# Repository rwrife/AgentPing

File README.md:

# AgentPing

**A tiny desk-side inbox for AI coding agents.**

AgentPing puts an animated 3D robot on either a **Waveshare ESP32-C6 Touch AMOLED 1.64** (280 × 456 portrait) or **Waveshare ESP32-S3-LCD-1.47B** (172 × 320 portrait). A Windows USB worker connects it to **Codex, Claude Code, and GitHub Copilot CLI**. Agent notifications show a provider logo and message; CLI and MCP controls let you play animations, pose limbs, and display custom icons.

The physical robot uses `live3d_usb` on C6 or `live3d_usb_s3` on S3. Both share the same robot, USB protocol, Windows client, and agent integrations. This path needs **USB only**: no Wi-Fi, .NET bridge, tray app, Node.js, or simulator is required.

| Board | Display / input | Firmware environment | Purchase |
| --- | --- | --- | --- |
| ESP32-C6-Touch-AMOLED-1.64 | 280 × 456 AMOLED, touch | `live3d_usb` | [Amazon](https://www.amazon.com/dp/B0GTDXXYV8) |
| ESP32-S3-LCD-1.47B | 172 × 320 LCD, **no touch** | `live3d_usb_s3` | [Amazon](https://www.amazon.com/dp/B0FBWPJPXN) / [Waveshare specifications](https://www.waveshare.com/ESP32-S3-LCD-1.47B.htm) |

The S3 passed [on-device smoke tests](firmware/BRINGUP-S3.md) for USB commands,
rendering and desktop controls. Physical LCD appearance and enclosure fit still
need verification. Select the exact **1.47B**, not the non-B S3 board.
The optional network/touch application remains C6-only. Board-specific
[3D-print enclosure files and fit notes](hardware/enclosure/README.md) are separate;
do not print the C6 enclosure for the S3.
Both enclosures share the C6 rounded snap-fit design and identical rear vents,
so the same [monitor arm and desktop stand](hardware/enclosure/mounts/README.md)
fit either version.

## Quick start: physical robot on Windows

### 1. Buy the board and prepare Windows

1. Choose either display board from the table above. Check the exact listing
   variant; a bare ESP32 development board or a different display revision
   will not work with these pin assignments and enclosure dimensions.
2. Have a USB **data** cable ready. The same connection powers the board and carries
   commands; a charge-only cable will not expose a serial port.
3. Install Git and Python 3.11 or newer (tested with 3.13), with their commands
   available on PATH. Open a new PowerShell terminal and check:

```powershell
git --version
python --version
```

Install and sign into your chosen agent CLIs separately. The USB Windows client
below is a background Python application controlled by `robot.cmd`; the optional
.NET tray application has separate instructions later in this guide.

### 2. Download the project and install the Windows USB client

```powershell
git clone https://github.com/rwrife/AgentPing.git
cd AgentPing
.\companion\setup-robot.ps1
```

Setup creates `.venv-robot` and installs the USB and MCP dependencies. Wait for
the `Ready` message, then check the launcher:

```powershell
.\companion\robot.cmd --help
```

If PowerShell blocks the setup script, perform the same installation directly:

```powershell
python -m venv .venv-robot
.\.venv-robot\Scripts\python.exe -m pip install -r tools/requirements-robot.txt
```

For an existing checkout, preserve local work, then use `git switch main` and
`git pull --ff-only`. Run setup again when Python dependencies change. All commands
below run from the repository root; virtual environment activation is unnecessary.

### 3. Build the firmware

Skip steps 3–4 if the board already has the current USB robot firmware for its model.
Create a separate build environment, install the pinned dependencies, and compile:

```powershell
python -m venv .venv-firmware
.\.venv-firmware\Scripts\python.exe -m pip install -r firmware/requirements-ci.txt
$firmwareEnv = "live3d_usb" # C6; use "live3d_usb_s3" for ESP32-S3-LCD-1.47B
.\.venv-firmware\Scripts\pio.exe run -d firmware -e $firmwareEnv
```

Wait for `[SUCCESS]`. The first build downloads the ESP-IDF toolchain and can take
several minutes. The output is `firmware/.pio/build/<environment>/firmware.bin`.
Use **`-e $firmwareEnv`** explicitly; the default C6 network firmware is a different
application. Model, textures, and animations are checked in, so FBX conversion,
Node.js, and the simulator are not needed. See [live renderer details](firmware/LIVE3D.md).

### 4. Connect and flash the board

1. Plug the board into the PC using the USB data cable.
2. Find its serial port in Device Manager under **Ports (COM & LPT)**, or run:

```powershell
.\.venv-robot\Scripts\python.exe -m serial.tools.list_ports
```

3. Replace `COM5` below with the reported port. Close serial monitors and stop an
   existing robot worker before flashing:

```powershell
# Only needed if a worker is already running:
.\companion\robot.cmd stop

.\.venv-firmware\Scripts\pio.exe run -d firmware -e $firmwareEnv -t upload --upload-port COM5
```

4. Wait for the upload's `[SUCCESS]` message and automatic reset. The robot should
   play its startup sequence and enter idle with the initial connection message.
   If no port appears, try another data cable/USB port before retrying.
   On S3, if automatic download fails, hold **BOOT**, tap **RESET**, release
   **BOOT**, and check the COM port again before uploading. Tap **RESET** after
   flashing if it remains in download mode. Keep both buttons clear of the enclosure.

### 5. Start the Windows USB client and verify the display

```powershell
.\companion\robot.cmd start
.\companion\robot.cmd status
```

A successful live response includes `"ok": true` and `VIEW state=...`. Wait a few seconds after plugging in or resetting the device before checking status. One background worker owns USB for both notifications and MCP.

```powershell
.\companion\robot.cmd worker-status  # Worker health and delivery counters
.\companion\robot.cmd reset          # Return to idle
.\companion\robot.cmd stop           # Release USB before flashing
```

Start the worker again after restarting Windows; setup does not install an automatic startup service. The initial connection caption disappears after the first desktop signal.

Send the first message:

```powershell
.\companion\robot.cmd message "Hello world!"
```

Look for `PAL STATE attention OK` in the command response and a waving robot with
a message bubble on the device. The client runs in the background, so no app window
is expected. Continue with the [terminal demo](#terminal-demo), then
[wire up your CLI agents](#wire-up-the-cli-agents) for automatic notices and MCP.

## Terminal demo

From the repository root, start the worker with `.\companion\robot.cmd start`.
Run the examples **one at a time**, leaving time to see each state. Sending the
next command replaces the current animation or message.

### Startup, thinking, and attention

```powershell
.\companion\robot.cmd state boot
.\companion\robot.cmd message "Consulting my rubber duck..." --state thinking
.\companion\robot.cmd message "Your approval is needed!"
.\companion\robot.cmd message "The changes are ready. Please review the pull request." --state attention
.\companion\robot.cmd reset
```

### Error messages

These demonstrate the error animation, close-up, and message bubble without
causing an actual failure:

```powershell
.\companion\robot.cmd message "Build failed: please check the terminal." --state error
.\companion\robot.cmd message "Tests failed. I need your help!" --state error
.\companion\robot.cmd message "Connection lost. Please check the USB cable." --state error
.\companion\robot.cmd reset
```

### Custom icons and Teams demo

```powershell
.\companion\robot.cmd icon --file assets/icons/heart-48.bin --color "#ff8800" --message "Hello world!"
.\companion\robot.cmd icon --file assets/icons/teams-48.bin --color "#8b88ff" --message "Teams: Your meeting starts now"
.\companion\robot.cmd icon --file assets/icons/enghub.bin --color "#0078D4" --message "EngHub: Your review is needed"

# Error state overrides the requested green/purple and renders the icon red.
.\companion\robot.cmd icon --file assets/icons/heart-48.bin --color "#00ff00" --state error --message "Demo error: something needs fixing!"
.\companion\robot.cmd icon --file assets/icons/teams-48.bin --color "#8b88ff" --state error --message "Teams demo: unable to join the meeting."
.\companion\robot.cmd reset
```

The Teams icon is a demo graphic; these commands do not connect to Teams.

### Dances and limb controls

```powershell
.\companion\robot.cmd dance chicken
.\companion\robot.cmd dance twist
.\companion\robot.cmd dance twist
.\companion\robot.cmd reset
.\companion\robot.cmd joint right_shoulder --z -90 --duration-ms 1000
.\companion\robot.cmd joint head --y 25 --duration-ms 800
.\companion\robot.cmd reset
```

### Short automatic demo

Paste this whole block to cycle through thinking, attention, and a red Teams-style
error icon, with six seconds to view each notice, then finish in idle:

```powershell
.\companion\robot.cmd start
.\companion\robot.cmd message "Thinking through the next step..." --state thinking
Start-Sleep -Seconds 6
.\companion\robot.cmd message "Ready for your review!" --state attention
Start-Sleep -Seconds 6
.\companion\robot.cmd icon --file assets/icons/teams-48.bin --color "#8b88ff" --state error --message "Demo error: please check the terminal."
Start-Sleep -Seconds 6
.\companion\robot.cmd reset
```

Messages and custom icons dismiss after 30 seconds and return to idle. Error icons are always red, overriding the requested color. Manual joint poses hold until reset or another state; offsets are relative to the captured animation pose. These move the rendered skeleton. Full command and bitmap details: [robot controls](docs/robot-control.md).

## Wire up the CLI agents

| Connection | Purpose | Setup |
| --- | --- | --- |
| Notification hooks | Automatically show permission/input requests, completion, and supported errors | Install hooks below |
| MCP tools | Let an agent deliberately show messages, dance, move joints, or send icons | Register MCP in each client |

Both share the USB worker. MCP registration alone does not install notification hooks. Hooks notify you; they do not approve, deny, or resume agent tasks.

Automatic thinking notices are limited to once every two minutes across all
agents. Repeats are dropped so the message can dismiss after 30 seconds and return
to idle. Attention and error notices still get through immediately. Explicit
CLI/MCP demo commands bypass this cooldown.

### Automatic notifications

Preview the configuration paths, then install the additive hooks for all three providers:

```powershell
.\.venv-robot\Scripts\python.exe tools/install_usb_hooks.py
.\.venv-robot\Scripts\python.exe tools/install_usb_hooks.py --apply
.\companion\robot.cmd start
```

The installer preserves unrelated handlers and backs up existing settings under `%USERPROFILE%\.agentping\usb\backups`.

| Agent | Configuration written | Events wired |
| --- | --- | --- |
| Codex | `%USERPROFILE%\.codex\hooks.json` | `UserPromptSubmit`, `PostToolUse`, `PermissionRequest`, `Stop` |
| Claude Code | `%USERPROFILE%\.claude\settings.json` | `PermissionRequest`, `Notification`, `Stop`, `StopFailure` |
| Copilot CLI | `%USERPROFILE%\.copilot\hooks\agentping-usb.json` | `userPromptSubmitted`, `permissionRequest`, `postToolUse`, `notification`, `awaitingUserInput`, `agentStop`, `errorOccurred` |

Restart your CLI sessions after installation. **In Codex, open `/hooks` and review/trust the AgentPing entries**; untrusted hooks are skipped. Rerun the installer after moving the checkout, replacing its Python environment, or updating the hook implementation.

Run a normal task in each agent, then check `robot.cmd worker-status` for an incremented provider delivery counter and inspect the display. Claude and Copilot live completion hooks were verified during bring-up. Codex's injected permission event was verified, but live Codex hook delivery still requires review/activation and validation in your session. See [notification details and tested versions](docs/usb-notifications.md).

For a **synthetic pipeline test**, not proof of a live agent event:

```powershell
'{}' | .\.venv-robot\Scripts\python.exe tools/agentping_usb_notifications.py hook --provider codex --event PermissionRequest
Start-Sleep -Seconds 2
.\companion\robot.cmd worker-status
```

### MCP registration in each CLI

**Copilot CLI on Windows:** this repository includes [`.github/mcp.json`](.github/mcp.json).
After installing the desktop tools, launch Copilot from the repository root:

```powershell
.\companion\robot.cmd start
copilot mcp list
copilot
```

Accept the repository trust prompt, then use `/mcp show agentping` to inspect the
connection. The configuration uses the relative `companion\robot.cmd` launcher,
so start Copilot in the repository root. No user-level registration is needed
for this checkout. The USB worker must already be running. Use the registration
commands below if you want the robot available from other repositories too.

With the worker running, resolve the checkout paths in PowerShell:

```powershell
$robotPython = (Resolve-Path .\.venv-robot\Scripts\python.exe).Path
$robotServer = (Resolve-Path .\tools\agentping_robot.py).Path
```

Run the registration command for each installed client you want to use:

```powershell
# Codex
codex mcp add agentping -- "$robotPython" "$robotServer" mcp
codex mcp list

# Claude Code: available across your projects
claude mcp add --transport stdio --scope user agentping -- "$robotPython" "$robotServer" mcp
claude mcp list

# GitHub Copilot CLI
copilot mcp add agentping -- "$robotPython" "$robotServer" mcp
copilot mcp list
```

Reconnect/restart the agent session and inspect its MCP tools. If an `agentping` entry exists, inspect/update it instead of registering a duplicate. For older Copilot CLI versions without `copilot mcp add`, use interactive `/mcp add`: local/stdio, the Python executable above, and the script path plus `mcp` as arguments.

Official references: [Codex MCP](https://developers.openai.com/codex/mcp), [Claude Code MCP](https://code.claude.com/docs/en/mcp), and [Copilot CLI MCP](https://docs.github.com/en/copilot/how-tos/copilot-cli/customize-copilot/add-mcp-servers). Command syntax was also checked against the installed CLIs.

For another MCP client, configure a **stdio** server with the Python executable as its command and `[absolute-script-path, "mcp"]` as its two arguments. A complete JSON example is in [robot-control.md](docs/robot-control.md#mcp-configuration). The client launches MCP; start the USB worker separately.

Available tools: `robot_status`, `robot_message`, `robot_animation`, `robot_dance`, `robot_move_joint`, `robot_icon`, and `robot_reset`.

Example demo prompts:

> Use AgentPing to show "Hello world!", then do the chicken dance.

> Reset the robot, turn its head 25 degrees on Y over 800 milliseconds, then reset it again.

> Show "Waiting for your approval" on the robot in the attention state.

> Use AgentPing's robot_message tool with state "error" to show "Build failed: please check the terminal." Leave it visible.

> Read assets/icons/teams-48.bin as hexadecimal and use AgentPing's robot_icon tool with color "#8b88ff", state "error", and message "Teams demo: unable to join the meeting." The device should show the icon in red.

> Use AgentPing's robot_reset tool to clear the demo and return to idle.

### Verify and troubleshoot

```powershell
# Software checks; no board required
.\.venv-robot\Scripts\python.exe -m unittest discover -s tools/tests

# MCP-to-device smoke test; changes poses/messages and ends in idle
.\.venv-robot\Scripts\python.exe tools/check_robot_mcp.py
```

- **USB unavailable/no acknowledgment:** check the data cable and USB port, close serial monitors, then run `robot.cmd stop`. Reconnect or reset the board, wait for boot, and run `robot.cmd start` followed by `robot.cmd status`. The worker finds the board by USB VID/PID, so it does not matter which port it is plugged into.
- **MCP tools missing:** check the registered absolute paths, reconnect the client, and confirm `.venv-robot` exists. MCP speaks a machine protocol over stdio; it does not present a terminal UI.
- **MCP works but automatic notices do not:** check hook installation and provider-session reload; review Codex `/hooks`. Compare delivery counters before/after a real event. Identical provider events can be coalesced for three seconds.
- **Firmware upload fails:** stop the worker and other serial clients, then flash the correct board environment (`live3d_usb` or `live3d_usb_s3`) on the correct port.

USB rendering, CLI/MCP control, provider logos, red error icons, and timed return to idle have been tested on the physical C6 device; the S3 needs the same bench checks. Notifications replace the visible notice; there is no on-device queue or approval-response flow.

## Forward Windows notifications

The Windows companion can send new notifications from selected apps to the USB
robot, including the app's logo and message. Open **Windows notifications** in the
packaged companion to grant access and select apps. Messages show for 30 seconds,
then the robot returns to idle.

See [Windows notification setup](docs/windows-notifications.md) for the Windows 11
package build/install commands, permission setup, and testing steps. The USB host
must be running; the network bridge is not required.

## Optional network bridge and tray application

### Build and launch the Windows tray app

This is the separate .NET management UI for the network bridge. It does not start
or replace the USB robot worker above. For the USB demo, use `robot.cmd`.

1. Install a **stable .NET 10.0 SDK**. `global.json` selects the latest installed
   10.0 feature band or patch (10.0.100 or newer).
   Confirm it appears in `dotnet --list-sdks`.
2. From the repository root, restore the solution and publish the app and its
   companion bridge together:

```powershell
dotnet restore AgentPing.sln --locked-mode
dotnet publish companion/AgentPing.Companion.Windows/AgentPing.Companion.Windows.csproj -c Release -r win-x64 --self-contained true --no-restore -o artifacts/win-x64/app
dotnet publish bridge/AgentPing.Bridge/AgentPing.Bridge.csproj -c Release -r win-x64 --self-contained true --no-restore -o artifacts/win-x64/app/bridge
```

3. Launch the published application:

```powershell
Start-Process -FilePath .\artifacts\win-x64\app\AgentPing.Companion.exe -WindowStyle Normal
```

4. Use its management window/tray icon for bridge controls. For ARM64 Windows,
   replace `win-x64` with `win-arm64` in all publish and launch paths.
   Keep the complete output folder, including `bridge/`, together when moving it.

Publishing self-contained includes the .NET runtime. These local builds are
unsigned. Network device pairing requires additional TLS/provisioning setup;
see [companion details](companion/README.md) and
[Windows troubleshooting](docs/windows-troubleshooting.md).

### Bridge

- ASP.NET Core 10 executable with structured JSON console logging
- loopback-only default listener at `http://127.0.0.1:8742`
- `GET /health` and non-secret protocol-v1 `GET /api/status`
- strict, 16 KiB-bounded `POST /api/events` and `POST /api/attentions` ingestion
- deterministic session/attention state, contiguous ingress ordering, idempotency, bounded history, transactional atomic persistence, stale-session handling, and restart recovery
- digest-authenticated protocol-v1 `/ws` capability negotiation, heartbeat validation, reconnect replay, and live state fan-out
- integration tests, process-level smoke coverage, and a reproducible Docker image build
- default-off, loopback-only adapters for Codex CLI, Claude Code, and Copilot CLI hooks, with bounded secret-redacted mapping, durable approve/deny outcomes, and synthetic fixtures

### Windows companion

- Windows Forms tray controls and live bridge/device/adapter/attention status
- explicit private-interface TLS pairing, bounded discovery, token rotation/revocation, and redacted log export
- current-user DPAPI credential protection, opt-in startup, high-DPI/accessibility metadata, and `.resx` localization extension points
- signed-ready WiX packaging plus explicitly unsigned `win-x64` and `win-arm64` CI artifacts

### Firmware

- pinned PlatformIO 6.1.18 / ESP-IDF 5.5.0 ESP32-C6 project with locked managed components
- compile-tested CO5300 AMOLED, FT6146 touch, and LVGL initialization from pinned Waveshare schematic/BSP evidence
- accessible disconnected/idle/running/waiting/completed/error UI with burn-in movement plus touch approve/deny/cancel/acknowledge/reply controls and two-tap destructive confirmation
- strict host-tested protocol parser/action policy/state reducer, authenticated WSS capability/heartbeat/replay/action transport, persistent resume state, and bounded reconnect backoff
- USB-serial NVS provisioning and physical factory reset with no hardcoded network/provider credentials or secret-bearing logs

### Protocol contract

- JSON Schema Draft 2020-12 contract for all nine v1 message kinds
- bounded envelopes, revisioned/idempotent actions, version negotiation, and reconnect/resume rules
- LAN threat model and full-entropy token pairing/rotation/revocation design
- golden valid/fail-closed fixtures consumed by Python validation and bridge serialization tests

The network firmware described in this section has compile/host-test evidence; USB robot validation does not validate its Wi-Fi, touch actions, or network pairing. The bridge implements protected credential lifecycle and TLS-only enrollment; operators must separately configure the RFC1918 Kestrel HTTPS/WSS endpoint and certificate. Provider permission decisions were not exercised with live provider accounts.

## Repository layout

```text
bridge/       ASP.NET Core bridge and tests
firmware/     shared robot, C6/S3 board drivers, native tests, and bring-up guides
protocol/     shared machine-readable protocol schema, fixtures, and validator
hardware/     hardware scope and future editable KiCad sources
docs/         architecture and protocol status
integration/  process-level integration tooling
scripts/      canonical local verification command
```

## Optional Pixel Pal portrait simulator

Preview the imported Meshy FBX and dynamic face states locally at the device's
280 × 456 portrait resolution. Run `npm ci` then `npm run dev` from `simulator/`
and open `http://127.0.0.1:5173`. See [simulator/README.md](simulator/README.md)
for controls, validation, asset provenance, and the strategy for moving to hardware.

## Build and test the bridge

Requires the .NET 10 SDK.

```bash
dotnet restore AgentPing.sln --locked-mode
dotnet build AgentPing.sln --configuration Release --no-restore
dotnet test AgentPing.sln --configuration Release --no-build
./integration/smoke-bridge.sh
```

Run the service:

```bash
dotnet run --project bridge/AgentPing.Bridge
curl http://127.0.0.1:8742/health
curl http://127.0.0.1:8742/api/status
```

Expected health response: `Healthy`. The status JSON identifies `agentping-bridge`, reports `status: ok`, uses protocol `apiVersion: 1.0`, and exposes only non-secret session/attention/history counts plus the latest server sequence. See [`bridge/README.md`](bridge/README.md) for ingestion, authenticated WebSocket, persistence, and configuration details.

## Build the firmware

```bash
python3 -m venv .venv-platformio
. .venv-platformio/bin/activate
python3 -m pip install --requirement firmware/requirements-ci.txt
python3 -m pip install --requirement protocol/requirements-ci.txt
firmware/tests/run_host_tests.sh
python3 protocol/validate.py
platformio run -d firmware
```

These commands build the C6 network firmware. CI compilation does not validate physical Wi-Fi, touch, or pairing behavior. Use the explicit board-specific USB instructions above for the robot. See [`firmware/README.md`](firmware/README.md).

## Container build

```bash
docker build --file bridge/AgentPing.Bridge/Dockerfile --tag agentping-bridge:local .
docker run --rm -p 127.0.0.1:8742:8742 agentping-bridge:local
```

The container listens on `0.0.0.0:8742` inside its isolated network namespace so Docker can forward traffic; the documented host publish is explicitly restricted to `127.0.0.1`.

## Architecture and protocol

The ESP32 remains a thin client; provider credentials stay on the PC. The bridge binds to loopback by default. LAN pairing requires a separately configured RFC1918 HTTPS/WSS endpoint and certificate; the default HTTP listener must never be exposed to the LAN.

- [`docs/architecture.md`](docs/architecture.md) describes current and planned boundaries.
- [`docs/protocol.md`](docs/protocol.md) specifies protocol v1, secure pairing, compatibility, ordering, resume, and fail-closed action rules.
- [`docs/generated/protocol-v1-reference.md`](docs/generated/protocol-v1-reference.md) is generated directly from the canonical schema.
- [`docs/provider-adapters.md`](docs/provider-adapters.md) documents default-off Codex CLI, Claude Code, Copilot CLI, and manual/test hook ingestion.
- [`docs/release/mvp-release-runbook.md`](docs/release/mvp-release-runbook.md), [`docs/release/security-privacy-review.md`](docs/release/security-privacy-review.md), [`docs/release/dependency-license-inventory.md`](docs/release/dependency-license-inventory.md), and [`docs/release/rollback-recovery.md`](docs/release/rollback-recovery.md) define MVP release gates and operations.
- [`hardware/README.md`](hardware/README.md) states the current hardware evidence and future KiCad scope.

## Contributing and security

See [`CONTRIBUTING.md`](CONTRIBUTING.md) for exact verification commands and [`SECURITY.md`](SECURITY.md) for private vulnerability reporting and trust-boundary requirements.

## License

MIT. See [`LICENSE`](LICENSE).

## Desktop robot controls

Use the [USB CLI and MCP server](docs/robot-control.md) to show custom messages,
play animations and dances, and pose individual robot joints from the desktop.

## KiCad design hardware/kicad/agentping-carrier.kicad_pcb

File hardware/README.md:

# Hardware

Hardware is separated by exact module: **Waveshare ESP32-C6-Touch-AMOLED-1.64**
and **Waveshare ESP32-S3-LCD-1.47B** (172 x 320 ST7789, no touch; not the non-B
model). Start with the [enclosure chooser](enclosure/README.md).

| Module | Standalone enclosure | Evidence status |
|---|---|---|
| C6 Touch AMOLED 1.64 | [Measured-board snap-fit pod](enclosure/esp32-c6-touch-amoled-1.64/README.md) | Original geometry/assets preserved: 9.3 mm user-measured stack, approximate 22 x 39 mm hole pattern, 42 x 56 x 15.1 mm housing |
| S3 LCD 1.47B | [C6-style snap-fit pod](enclosure/esp32-s3-lcd-1.47b/README.md) | Manufacturer 20.32 x 36.37 mm PCB; user-measured 7.7 mm stack; two-piece 42 x 56 x 12.5 mm unprinted prototype with glass-envelope/retention limits |

The optional low-voltage **Rev A0 carrier below remains C6-only**. It has not
been adapted to the S3 pinout or mounting layout. Neither small standalone
enclosure fits this 70 x 60 mm carrier. No RF design is modified.

Both enclosures retain the exact C6 rear vent interface for future use:
**four 10 x 2 mm rectangular slots on 6 mm pitch**, x = -5..5 and lower Y
edges = -8, -2, 4, 10 mm, through a **2.8 mm rear floor**. C6 artifacts remain
unchanged. The S3 copies these dimensions; any physical board/accessory conflict
must be reported rather than resolved by changing the vents.

## Rev A0 carrier

The carrier accepts USB-C 5 V power, protects it with a 500 mA hold PPTC,
TVS, and reverse-current diode, then feeds only the module's USB 5 V header
pin. An optional GPIO6-controlled low-side MOSFET drives a separately
connected haptic load limited to 150 mA. It is a SELV, desk-use interface:
there is no mains, battery charger, high-voltage, medical, life-safety, or
RF-module redesign scope.

| Artifact | Purpose |
|---|---|
| [`kicad/agentping-carrier.kicad_pro`](kicad/agentping-carrier.kicad_pro) | KiCad 9 project and DRC rules |
| [`kicad/agentping-carrier.kicad_sch`](kicad/agentping-carrier.kicad_sch) | Editable schematic; symbol properties are the BOM source of truth |
| [`kicad/agentping-carrier.kicad_pcb`](kicad/agentping-carrier.kicad_pcb) | Editable two-layer PCB, routing, zones, and rule areas |
| [`bom/agentping-carrier-bom.csv`](bom/agentping-carrier-bom.csv) | Generated schematic-backed BOM with MPNs, source URLs, and preliminary costs |
| [`fabrication/rev-a0/`](fabrication/rev-a0/) | KiCad 9.0.9 Gerbers, drills, position data, IPC-2581, STEP, schematic/assembly PDFs, and integrity hashes |
| [`references/MANIFEST.md`](references/MANIFEST.md) | Manufacturer evidence, revision dates, and mechanical source traceability |
| [`reports/generated/`](reports/generated/) | Reproducible KiCad 9.0.9 ERC and DRC reports |

## Electrical and interface constraints

| Interface | Defined constraint |
|---|---|
| USB-C J3 | Power-only USB-C sink. CC1 and CC2 use 5.1 kOhm Rd to GND; D+/D-, SBU, and all non-power module USB pins are intentionally unconnected. |
| Power path | J3 VBUS -> D1 TVS -> F1 PPTC -> D2 reverse-current block -> `+5V_MODULE` / module P2 pin 10. The design ceiling is 500 mA hold; actual module current and inrush still require bench measurement. |
| Module sockets | J1/P1 and J2/P2 are 1x10 2.54 mm sockets. The carrier uses J1 pin 8 (`GPIO6`) and GND pins, plus J2 pin 10 (USB 5 V) and GND pins only. |
| Haptic J4 | Pin 1 is protected 5 V; pin 2 is Q1's switched low side. Q1 defaults off through R4 and is gated through R3. Use only a <=150 mA load with appropriate physical and acoustic evaluation. |
| Test points | VBUS, protected 5 V, GND, GPIO6, Q1 gate, and haptic low side are exposed as unpopulated test pads. |
| Design rules | Two-layer, 1.6 mm board; 0.20 mm minimum track/clearance, 0.50 mm power tracks, 0.60/0.30 mm via/drill, 0.50 mm copper-to-edge clearance. |

## RF and mechanical boundaries

The board is 70 x 60 mm. Four M3 carrier mounting-hole centers are at
(4,4), (66,4), (4,56), and (66,56) mm from the lower-left board origin.
The module M2 centers are (9,10.25), (31,10.25), (9,48.75), and
(31,48.75) mm. The supplied module STEP model and dimensions PDF are
traceable in the reference manifest.

Both copper layers define a 17 x 45 mm `WAVESHARE MODULE RF` rule area
(x=11.5..28.5, y=7.5..52.5 mm) prohibiting pours, tracks, vias, and pads.
A nested module-body rule area also prohibits component placement. These
enforce a conservative copper-free module region in KiCad rather than relying
on an assembly instruction alone. Do not move, reduce, or override either
keepout without reviewing the specific Waveshare module revision and RF
evidence.

## Assemble and bring up

1. Assemble the USB-C power/protection path (J3, R1/R2, D1, F1, D2, C1)
and verify no short between VBUS and GND before inserting the module.
2. Apply a current-limited 5 V USB-C source; verify the protected 5 V test
point and confirm D2 prevents reverse feed toward J3.
3. Remove power, install the Waveshare module in J1/J2 with its pin-1
orientation matched to the silkscreen/assembly drawing, then bring up the
firmware using [`../firmware/BRINGUP.md`](../firmware/BRINGUP.md).
4. Populate the optional haptic path only after confirming GPIO6 remains off
during reset and the chosen load measures no more than 150 mA.

Mating JST PH housing/contacts, USB-C cable, Waveshare module, haptic
actuator, screws, standoffs, and enclosure are external ordering items; see
the BOM comments. The carrier contains no provider credentials and must not
be used to transfer them.

## Reproducible checks and fabrication exports

For both standalone enclosures, run the read-only FreeCAD check independently
of KiCad:

```powershell
& 'C:\Program Files\FreeCAD 1.1\bin\python.exe' hardware\enclosure\verify_enclosures.py
```

It checks C6 preservation hashes, solid/mesh validity, assembled C6 overlap,
and the S3 tray/bezel, part overlap, 0.3 mm assumed-envelope glass clearance,
button keepouts and common rear vents. Physical fit and retention remain unverified.
The carrier-only `verify.sh` does not claim to validate enclosure geometry.

KiCad CLI 9.0.9 was used for the checked-in reports and fabrication snapshot.
Run the checks from the repository root:

```bash
python3 -m venv /tmp/agentping-kicad-venv
/tmp/agentping-kicad-venv/bin/python -m pip install \
  --requirement hardware/kicad/requirements.txt
PYTHON_BIN=/tmp/agentping-kicad-venv/bin/python ./hardware/verify.sh
```

`verify.sh` checks that the BOM is generated from the schematic, reruns ERC
and DRC with violations treated as errors, and verifies the fabrication
snapshot hashes. It is tool-clean evidence, not physical validation.

To write a new, unversioned KiCad export set without replacing the reviewed
`rev-a0` snapshot:

```bash
./hardware/kicad/export_fabrication.sh hardware/fabrication/candidate
```

The generator scripts are maintained design-data regeneration aids. Their
schematic-generation path requires a KiCad 9 symbol-library installation in
addition to `requirements.txt`; the checked-in schematic and PCB are the
authoritative editable engineering sources and can be opened directly in
KiCad 9.

## Evidence limits

No physical PCB, assembly, USB-C interoperability, current/inrush,
haptic/acoustic, temperature, enclosure fit, RF, antenna, display, touch, or
firmware-on-carrier test has been performed for Rev A0. The BOM prices are
preliminary estimates, not quotes or stock checks. A clean ERC/DRC and
generated fabrication files demonstrate only that the current design passed
those KiCad checks. The KiCad 9.0.9 export environment used for the candidate
export did not provide the legacy `KICAD6_3DMODEL_DIR` /
`KICAD7_3DMODEL_DIR` component-model variables, so its generated STEP contains
the board solid but omits affected library component bodies. Use the supplied
Waveshare STEP model for enclosure work, and configure the matching KiCad 3D
model libraries before relying on an assembled carrier STEP.

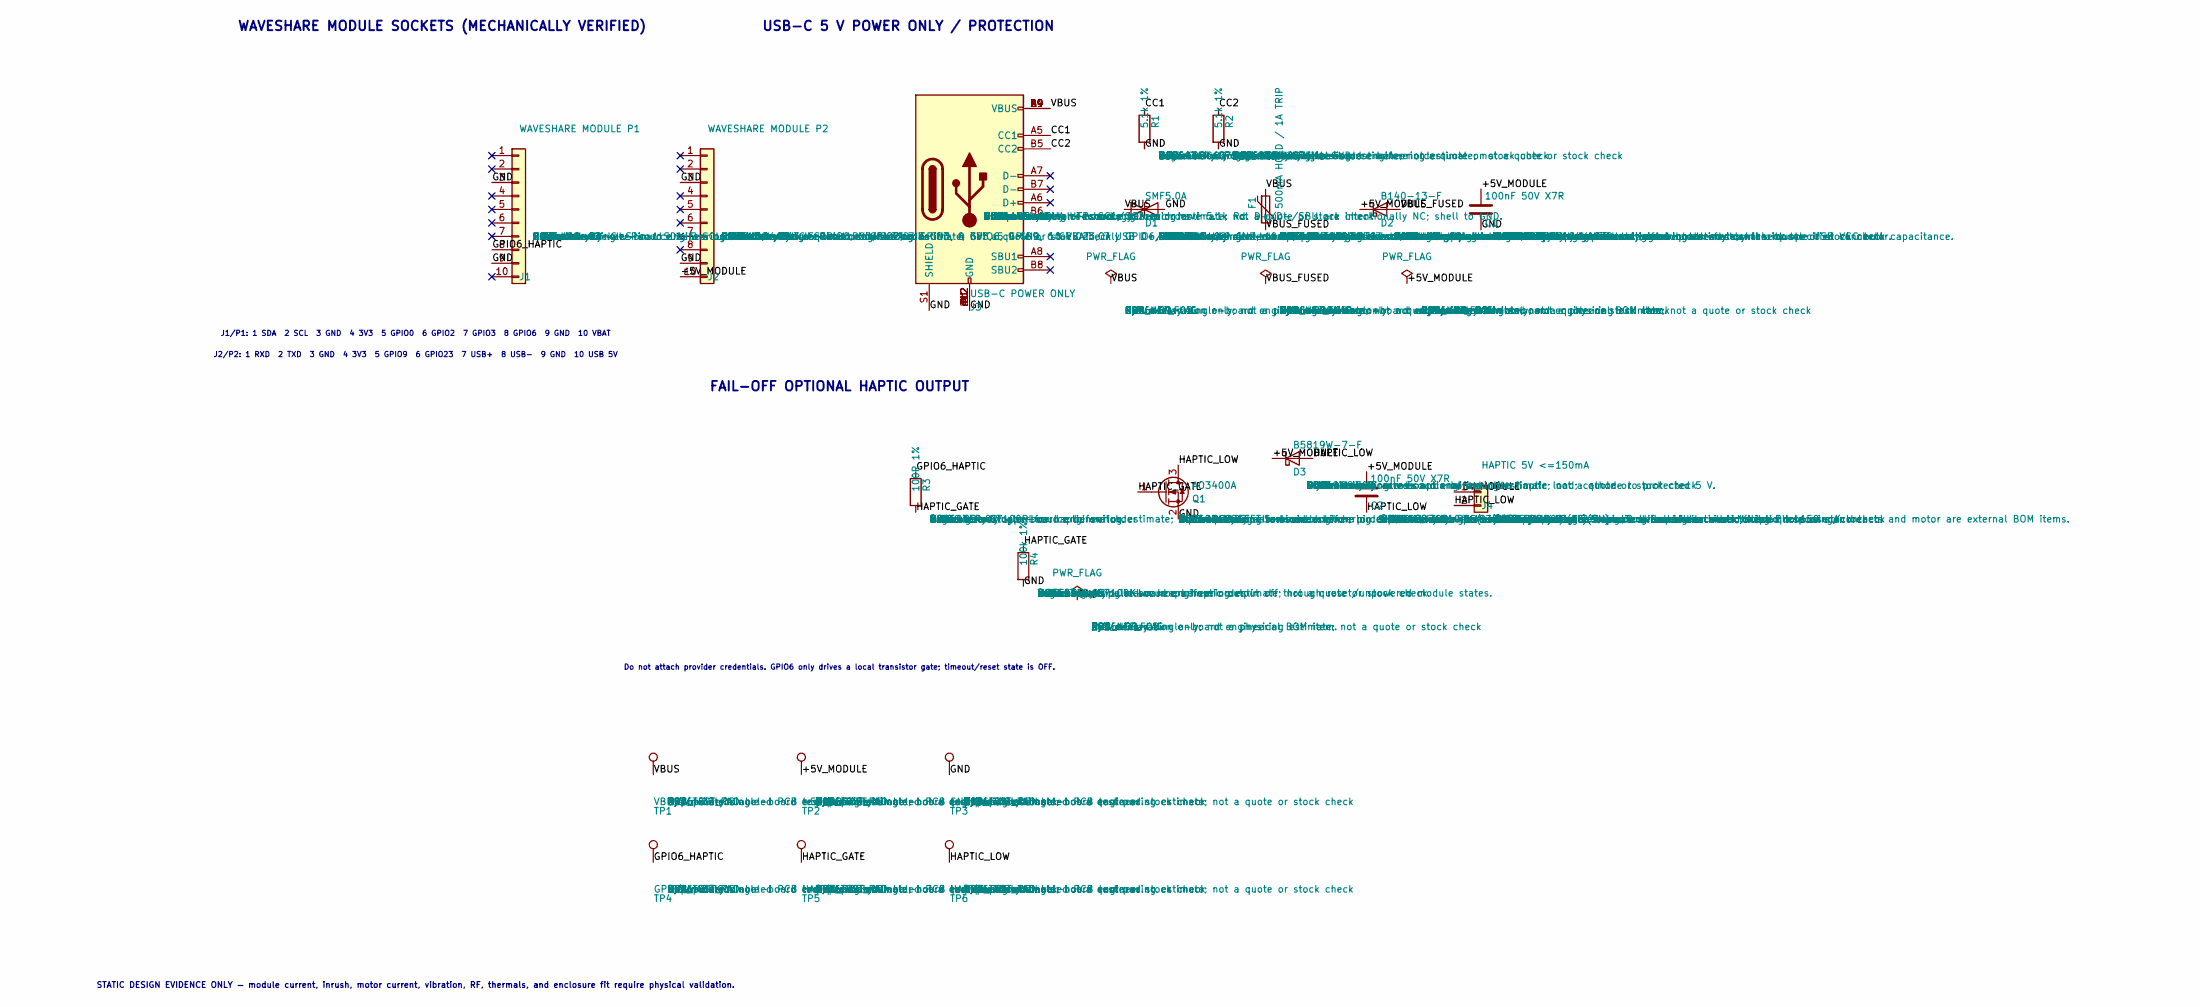
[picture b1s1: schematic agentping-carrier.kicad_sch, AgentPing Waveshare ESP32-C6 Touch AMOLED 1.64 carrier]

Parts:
C1, C2: 100nF 50V X7R; C_0603_1608Metric; MPN GRM188R71H104KA93D
D1: SMF5.0A; D_SOD-123F; MPN SMF5.0A
D2: B140-13-F; D_SMA; MPN B140-13-F
D3: B5819W-7-F; D_SOD-123; MPN B5819W-7-F
F1: 500mA HOLD / 1A TRIP; Fuse_1812_4532Metric; MPN MF-MSMF050-2
J1: WAVESHARE MODULE P1; PinSocket_1x10_P2.54mm_Vertical; MPN SSW-110-02-G-S
J2: WAVESHARE MODULE P2; PinSocket_1x10_P2.54mm_Vertical; MPN SSW-110-02-G-S
J3: USB-C POWER ONLY; USB_C_Receptacle_GCT_USB4105-xx-A_16P_TopMnt_Horizontal; MPN USB4105-GF-A
J4: HAPTIC 5V <=150mA; JST_PH_B2B-PH-K_1x02_P2.00mm_Vertical; MPN B2B-PH-K-S(LF)(SN)
Q1: AO3400A; SOT-23; MPN AO3400A
R1, R2: 5.1k 1%; R_0603_1608Metric; MPN RC0603FR-075K1L
R3: 100R 1%; R_0603_1608Metric; MPN RC0603FR-07100RL
R4: 100k 1%; R_0603_1608Metric; MPN RC0603FR-07100KL
TP1: VBUS; TestPoint_Pad_D1.5mm; MPN PCB_TEST_PAD
TP2: +5V_MODULE; TestPoint_Pad_D1.5mm; MPN PCB_TEST_PAD
TP3: GND; TestPoint_Pad_D1.5mm; MPN PCB_TEST_PAD
TP4: GPIO6_HAPTIC; TestPoint_Pad_D1.5mm; MPN PCB_TEST_PAD
TP5: HAPTIC_GATE; TestPoint_Pad_D1.5mm; MPN PCB_TEST_PAD
TP6: HAPTIC_LOW; TestPoint_Pad_D1.5mm; MPN PCB_TEST_PAD

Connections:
/+5V_MODULE: C1.1, C2.1, D2.1 (K), D3.1 (K), J2.10, J4.1, TP2.1
/CC1: J3.A5 (CC1), R1.1
/CC2: J3.B5 (CC2), R2.1
/GND: C1.2, D1.2 (A2), J1.3, J1.9, J2.3, J2.9, J3.A1 (GND), J3.A12 (GND), J3.B1 (GND), J3.B12 (GND), J3.S1 (SHIELD), Q1.2 (S), R1.2, R2.2, R4.2, TP3.1
/GPIO6_HAPTIC: J1.8, R3.1, TP4.1
/HAPTIC_GATE: Q1.1 (G), R3.2, R4.1, TP5.1
/HAPTIC_LOW: C2.2, D3.2 (A), J4.2, Q1.3 (D), TP6.1
/VBUS: D1.1 (A1), F1.1, J3.A4 (VBUS), J3.A9 (VBUS), J3.B4 (VBUS), J3.B9 (VBUS), TP1.1
/VBUS_FUSED: D2.2 (A), F1.2

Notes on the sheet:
WAVESHARE MODULE SOCKETS (MECHANICALLY VERIFIED)
USB-C 5 V POWER ONLY / PROTECTION
FAIL-OFF OPTIONAL HAPTIC OUTPUT
J1/P1: 1 SDA 2 SCL 3 GND 4 3V3 5 GPIO0 6 GPIO2 7 GPIO3 8 GPIO6 9 GND 10 VBAT
J2/P2: 1 RXD 2 TXD 3 GND 4 3V3 5 GPIO9 6 GPIO23 7 USB+ 8 USB- 9 GND 10 USB 5V
Do not attach provider credentials. GPIO6 only drives a local transistor gate; timeout/reset state is OFF.
STATIC DESIGN EVIDENCE ONLY — module current, inrush, motor current, vibration, RF, thermals, and enclosure fit require physical validation.

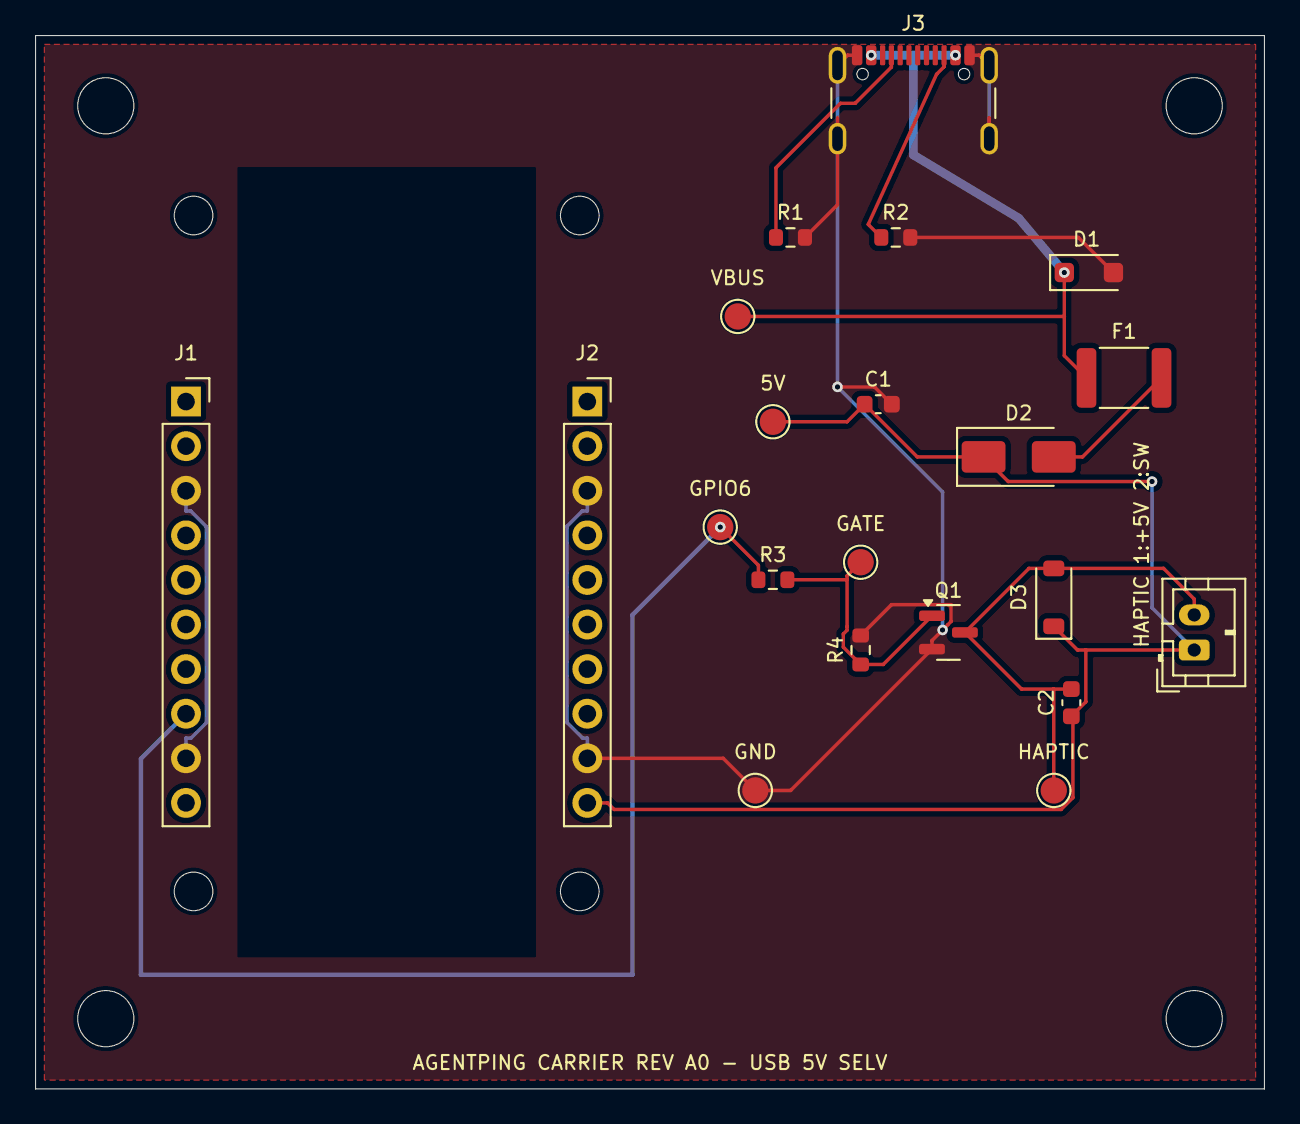
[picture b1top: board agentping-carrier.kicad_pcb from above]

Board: 2 copper layers, 70.0 x 60.0 mm, 29 parts (0 on the bottom side), 9 nets.

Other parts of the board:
H1, H2, H3, H4: CARRIER M3; MountingHole_3.2mm_M3
HM1, HM2, HM3, HM4: WAVESHARE MODULE M2; MountingHole_2.2mm_M2

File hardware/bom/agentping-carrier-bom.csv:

Reference,Qty,Value,Footprint,Manufacturer,MPN,Supplier,Supplier PN,Estimated Unit Cost USD,Extended Cost USD,Cost Basis,Datasheet,Datasheet Checked UTC,BOM Comments
"C1,C2",2,100nF 50V X7R,Capacitor_SMD:C_0603_1608Metric,Murata,GRM188R71H104KA93D,Estimate only — re-source before order,Not checked,0.02,0.0400,Preliminary single-board engineering estimate; not a quote or stock check,https://search.murata.co.jp/Ceramy/image/img/A01X/G101/ENG/G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,2026-09-02,High-frequency bypass only; module already carries its specified VCC bulk capacitance. | Optional motor-terminal RF suppression capacitor; evaluate acoustic/haptic response on bench.
D1,1,SMF5.0A,Diode_SMD:D_SOD-123F,Littelfuse,SMF5.0A,Estimate only — re-source before order,Not checked,0.30,0.3000,Preliminary single-board engineering estimate; not a quote or stock check,https://www.littelfuse.com/assetdocs/tvs-diodes-smf-datashee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,2026-09-02,5 V VBUS transient clamp; place beside J3 with short ground return.
D2,1,B140-13-F,Diode_SMD:D_SMA,Diodes Incorporated,B140-13-F,Estimate only — re-source before order,Not checked,0.09,0.0900,Preliminary single-board engineering estimate; not a quote or stock check,https://www.diodes.com/assets/Datasheets/ds13002.pdf,2026-09-02,Series reverse-current block; carrier USB must not be back-fed by the module USB connector.
D3,1,B5819W-7-F,Diode_SMD:D_SOD-123,Diodes Incorporated,B5819W-7-F,Estimate only — re-source before order,Not checked,0.10,0.1000,Preliminary single-board engineering estimate; not a quote or stock check,https://www.diodes.com/assets/Datasheets/ds30217.pdf,2026-09-02,Flyback diode across optional inductive haptic load; cathode to protected 5 V.
F1,1,500mA HOLD / 1A TRIP,Fuse:Fuse_1812_4532Metric,Bourns,MF-MSMF050-2,Estimate only — re-source before order,Not checked,0.07,0.0700,Preliminary single-board engineering estimate; not a quote or stock check,https://www.bourns.com/docs/product-datasheets/mf-msmf.pdf,2026-09-02,500 mA hold PPTC enforces the provisional USB default-current ceiling.
J1,1,WAVESHARE MODULE P1,Connector_PinSocket_2.54mm:PinSocket_1x10_P2.54mm_Vertical,Samtec,SSW-110-02-G-S,Estimate only — re-source before order,Not checked,2.00,2.0000,Preliminary single-board engineering estimate; not a quote or stock check,https://suddendocs.samtec.com/prints/ssw-1xx-xx-xxx-x-xx-xx-mkt.pdf,2026-09-02,"P1 female socket. Pin 1 SDA, 2 SCL, 3 GND, 4 3V3, 5 GPIO0, 6 GPIO2, 7 GPIO3, 8 GPIO6, 9 GND, 10 VBAT. Only GPIO6/GND used by carrier."
J2,1,WAVESHARE MODULE P2,Connector_PinSocket_2.54mm:PinSocket_1x10_P2.54mm_Vertical,Samtec,SSW-110-02-G-S,Estimate only — re-source before order,Not checked,2.00,2.0000,Preliminary single-board engineering estimate; not a quote or stock check,https://suddendocs.samtec.com/prints/ssw-1xx-xx-xxx-x-xx-xx-mkt.pdf,2026-09-02,"P2 female socket. Pin 1 RXD, 2 TXD, 3 GND, 4 3V3, 5 GPIO9, 6 GPIO23, 7 USB D+, 8 USB D-, 9 GND, 10 USB 5V. Carrier uses GND and diode-isolated USB 5V only."
J3,1,USB-C POWER ONLY,Connector_USB:USB_C_Receptacle_GCT_USB4105-xx-A_16P_TopMnt_Horizontal,Global Connector Technology,USB4105-GF-A,Estimate only — re-source before order,Not checked,1.10,1.1000,Preliminary single-board engineering estimate; not a quote or stock check,https://gct.co/files/drawings/usb4105.pdf,2026-09-02,5 V power-only UFP. CC1/CC2 each have 5.1k Rd. D+/D-/SBU are intentionally NC; shell to GND.
J4,1,HAPTIC 5V <=150mA,Connector_JST:JST_PH_B2B-PH-K_1x02_P2.00mm_Vertical,JST,B2B-PH-K-S(LF)(SN),Estimate only — re-source before order,Not checked,0.15,0.1500,Preliminary single-board engineering estimate; not a quote or stock check,https://www.jst-mfg.com/product/pdf/eng/ePH.pdf,2026-09-02,"Pin 1 protected 5 V, pin 2 switched low side. Mating PH housing/contacts and motor are external BOM items."
Q1,1,AO3400A,Package_TO_SOT_SMD:SOT-23,Alpha & Omega Semiconductor,AO3400A,Estimate only — re-source before order,Not checked,0.10,0.1000,Preliminary single-board engineering estimate; not a quote or stock check,https://aosmd.com/res/data_sheets/AO3400A.pdf,2026-09-02,"30 V N-MOSFET low-side switch; pin 1 G, 2 S, 3 D. RDS(on) is specified at 2.5 V gate drive. Limit connector load to 150 mA."
"R1,R2",2,5.1k 1%,Resistor_SMD:R_0603_1608Metric,Yageo,RC0603FR-075K1L,Estimate only — re-source before order,Not checked,0.02,0.0400,Preliminary single-board engineering estimate; not a quote or stock check,https://www.yageo.com/upload/media/product/productsearch/dat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,2026-09-02,USB-C CC1 Rd to GND. | USB-C CC2 Rd to GND.
R3,1,100R 1%,Resistor_SMD:R_0603_1608Metric,Yageo,RC0603FR-07100RL,Estimate only — re-source before order,Not checked,0.02,0.0200,Preliminary single-board engineering estimate; not a quote or stock check,https://www.yageo.com/upload/media/product/productsearch/dat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,2026-09-02,GPIO6 gate stopper for haptic switch.
R4,1,100k 1%,Resistor_SMD:R_0603_1608Metric,Yageo,RC0603FR-07100KL,Estimate only — re-source before order,Not checked,0.02,0.0200,Preliminary single-board engineering estimate; not a quote or stock check,https://www.yageo.com/upload/media/product/productsearch/dat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,2026-09-02,MOSFET gate pulldown keeps haptic output off through reset/unpowered module states.
